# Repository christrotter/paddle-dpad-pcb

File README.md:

# 2025/11/23 update
So the 1.1 version is actually wrong, 1.0 version works fine.  The issue was that the dpad (led-pad) was incorrectly pinned, so using led-pad-1.1 and paddle-dpad-1.0 works.

# paddle-inator
A prototype pcb to mount ALPS SKRHACE010 switches on the back of the thumbcluster and use them as soft-action paddle-keys.  Uses an SK6805-EC15 led indicator and 12-pin 0.5mm pitch FFC connector - I'm trying to move away from single-wire soldering.

The application I'll be trying these out in is for 'curl your fingers inwards' paddle switches, but I needed a very soft touch due to fibromyalgia.

I've been using the SKRHACE010 5-way switches in my dpads and they are wonderful with enough leverage.  I prototyped using an old pcb with that switch and so far seems like this will work just fine.

# Usage example
The actual use case in-model might help to clarify the functionality.  There are three of these paddles just between the thumb keys and main keywell.

# Connector wiring details
- 3 GND pins, 1 5v pin
- 6 pins for the switch (_even though I only really use one_)
- DI & DO for led signal

# PCB details
- 14.2 x 23.9mm (_why? b/c I wasn't aiming for a specific dimension, just 'small as reasonable'_)
- 1mm radius corners

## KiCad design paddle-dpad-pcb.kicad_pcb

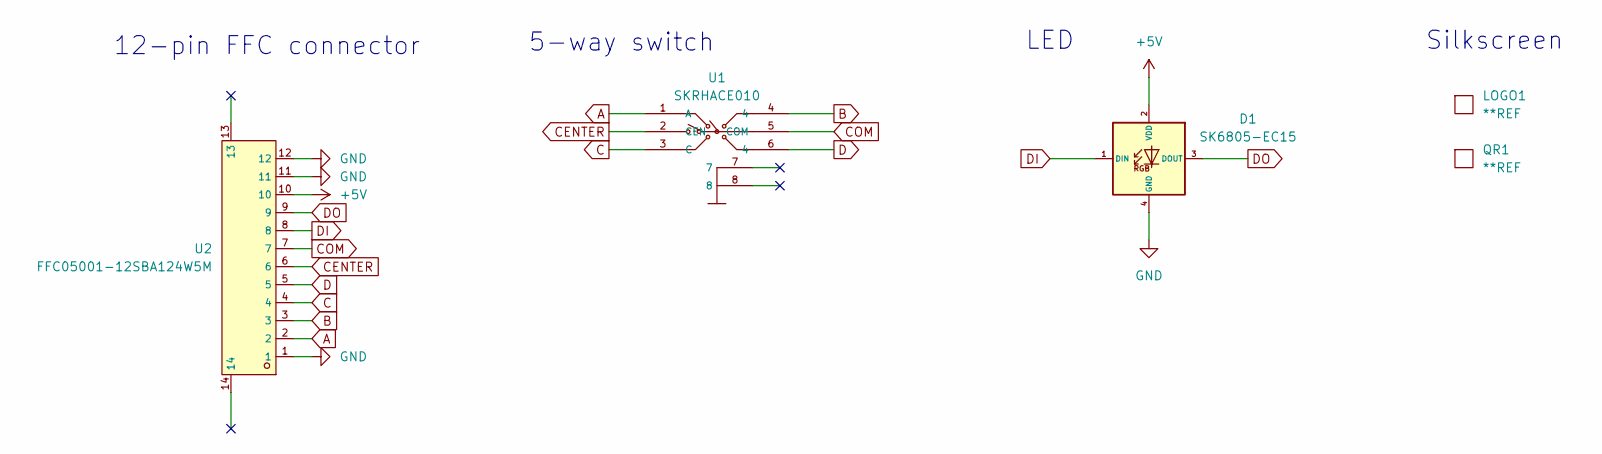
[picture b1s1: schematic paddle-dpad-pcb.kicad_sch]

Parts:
D1: SK6805-EC15; LED-SMD_4P-L1.5-W1.5-BL; MPN SK6805-EC15; LCSC C2890035
LOGO1: **REF; awesome-logo
QR1: **REF; paddle-dpad-pcb-qr-10mm
U1: SKRHACE010; SW-SMD_SKRHACE010; LCSC C209766
U2: FFC05001-12SBA124W5M; FFC-SMD_FFC05001-12SBA124W5M; LCSC C2833760

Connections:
+5V: D1.2 (VDD), U2.10
A: U1.1 (A), U2.2
B: U1.4, U2.3
C: U1.3 (C), U2.4
CENTER: U1.2 (CEN), U2.6
COM: U1.5 (COM), U2.7
D: U1.6 (4), U2.5
DI: D1.1 (DIN), U2.8
DO: D1.3 (DOUT), U2.9
GND: D1.4 (GND), U2.1, U2.11, U2.12

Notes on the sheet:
12-pin FFC connector
Silkscreen
LED
5-way switch

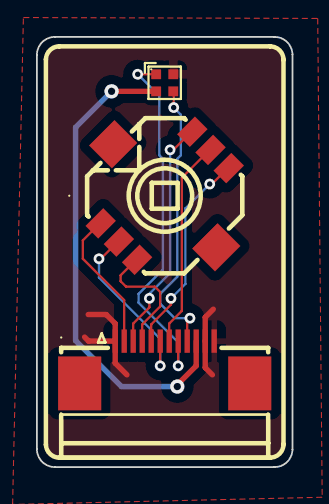
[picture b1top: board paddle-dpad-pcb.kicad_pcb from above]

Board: 2 copper layers, 14.2 x 23.9 mm, 5 parts (2 on the bottom side), 10 nets.

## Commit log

2025-07-12 submitted first rev to jlc
2025-07-12 adding step file
2025-07-12 updating readme
2025-07-12 minor updates
